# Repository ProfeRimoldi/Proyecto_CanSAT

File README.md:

# Proyecto CanSat – Base Aérea El Palomar

Sistema electrónico para misión tipo CanSat desarrollado en la EEST N°4 I Brigada Aérea El Palomar, orientado al diseño, validación y documentación de hardware y firmware para sistemas embarcados aeroespaciales.

Este repositorio centraliza el desarrollo de:

* Onboard Computer (OBC)
* Earth Station Dev Board
* Firmware ESP32
* Documentación técnica
* Revisiones de fabricación de PCB

---

## Estructura del proyecto

```text
Proyecto_CanSAT/
├── hardware/
│   ├── Onboard_Comp/
│   │   ├── kicad/
│   │   ├── outputs/
│   │   │   └── Rev_A/
│   │   └── docs/
│   │
│   └── Earth_Station/
│       ├── kicad/
│       ├── outputs/
│       └── docs/
│
├── firmware/
│
├── docs/
│
└── README.md
```

---

## Hardware

### Onboard Computer (OBC)

Computadora principal embarcada encargada de:

* adquisición de sensores
* telemetría
* control de misión
* gestión de eventos de vuelo
* integración con estación terrestre

Actualmente cuenta con:

* diseño PCB en KiCad
* esquemático jerárquico
* revisión formal de fabricación `Rev_A`
* Gerbers
* Drill files
* BOM
* PDF de esquemático
* renders e imágenes técnicas

---

### Earth Station Dev Board

Placa de desarrollo para estación terrestre destinada a:

* recepción de telemetría
* configuración de parámetros
* validación de comunicaciones
* integración de subsistemas

Actualmente cuenta con:

* diseño PCB en KiCad
* documentación estructurada
* revisión formal de fabricación `Rev_A`
* Gerbers
* Drill files
* BOM
* PDF de esquemático
* renders e imágenes técnicas

---

## Firmware

Desarrollo basado en ESP32 para:

* adquisición de datos
* control de sensores
* comunicaciones
* telemetría
* lógica de misión

Actualmente cuenta con:

* Firmware Test, verificador de enlace de comunicación LoRa entre los módulos.
* Muestra en pantalla, firmware dedicado a enviar los datos de aceleración en 3 ejes, y un código en Processing para visualizarlo.
* TestLED, para verificar el funcionamiento de los periféricos en la Earth Station Dev Board.

La estructura de firmware se encuentra en evolución y será versionada junto con las revisiones de hardware.

---

## Gestión de revisiones

Las revisiones de fabricación se organizan mediante:

```text
outputs/Rev_A/
outputs/Rev_B/
outputs/Rev_C/
```

permitiendo trazabilidad completa entre:

* diseño fuente
* fabricación real
* validaciones de laboratorio
* mejoras de revisión

---

## Objetivo

Mantener una metodología de desarrollo profesional para proyectos electrónicos aeroespaciales, con trazabilidad completa de hardware, firmware y documentación técnica.

---

## Autor

Damián Rimoldi
Ingeniería Electrónica – UTN FRH
GLT – Grupo de Lanzadores Tecnológicos
EEST N°4 I Brigada Aérea El Palomar

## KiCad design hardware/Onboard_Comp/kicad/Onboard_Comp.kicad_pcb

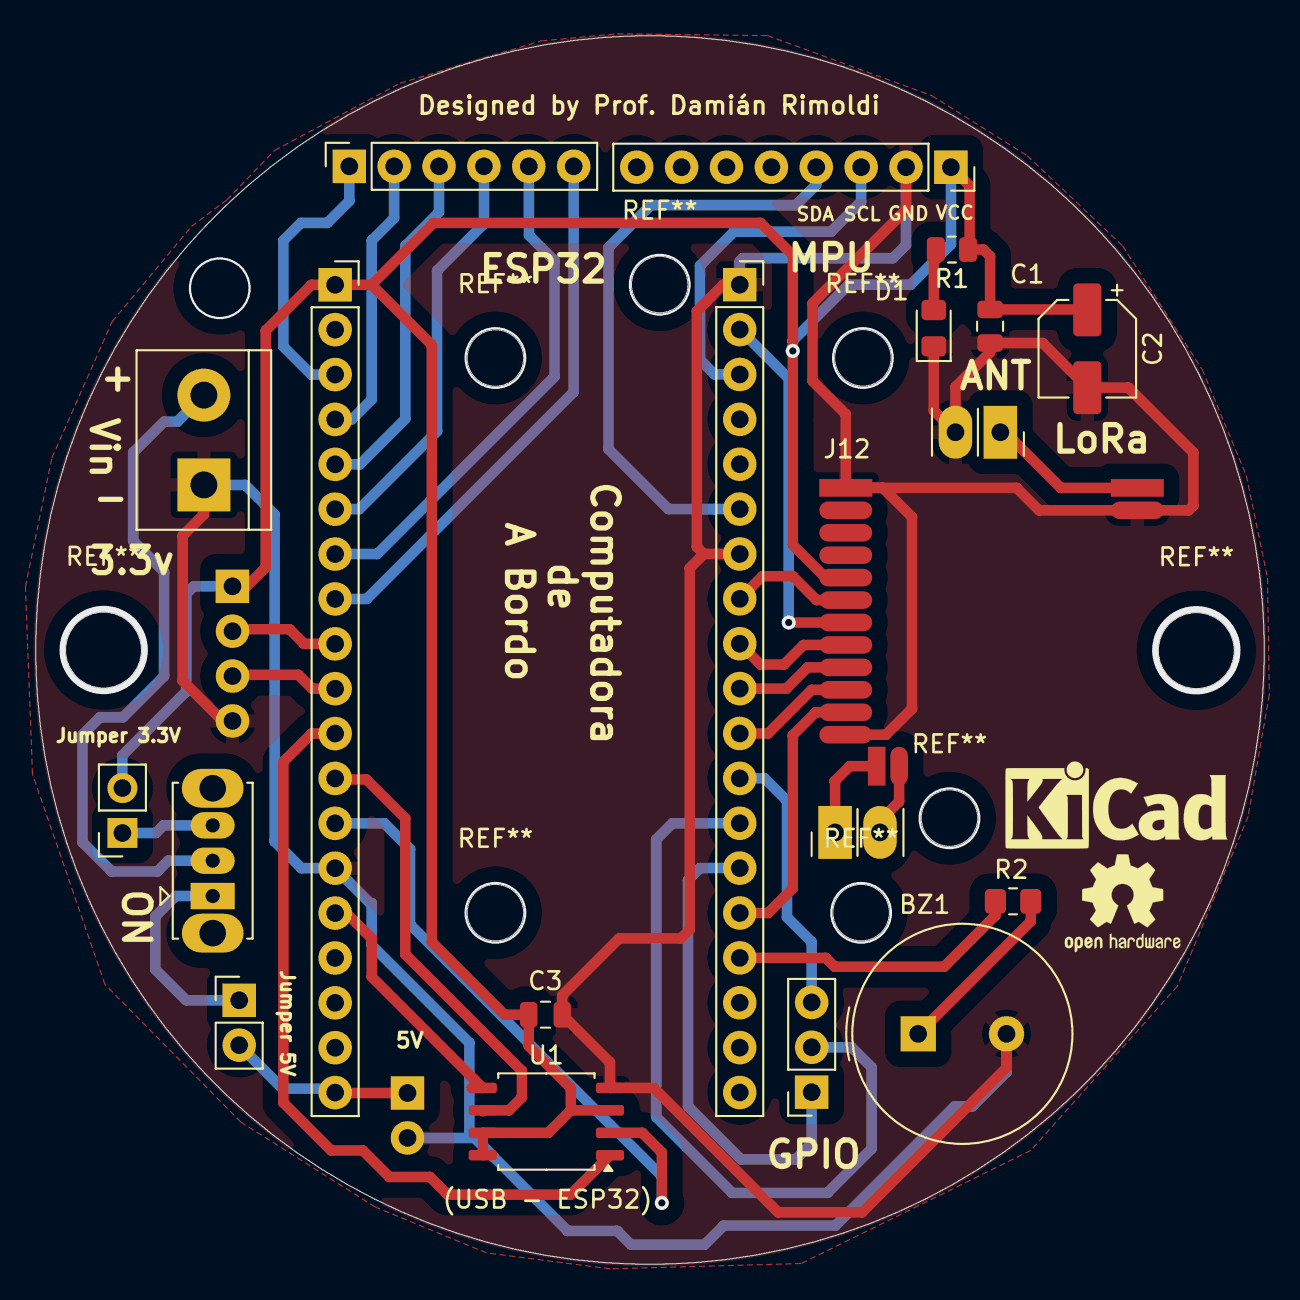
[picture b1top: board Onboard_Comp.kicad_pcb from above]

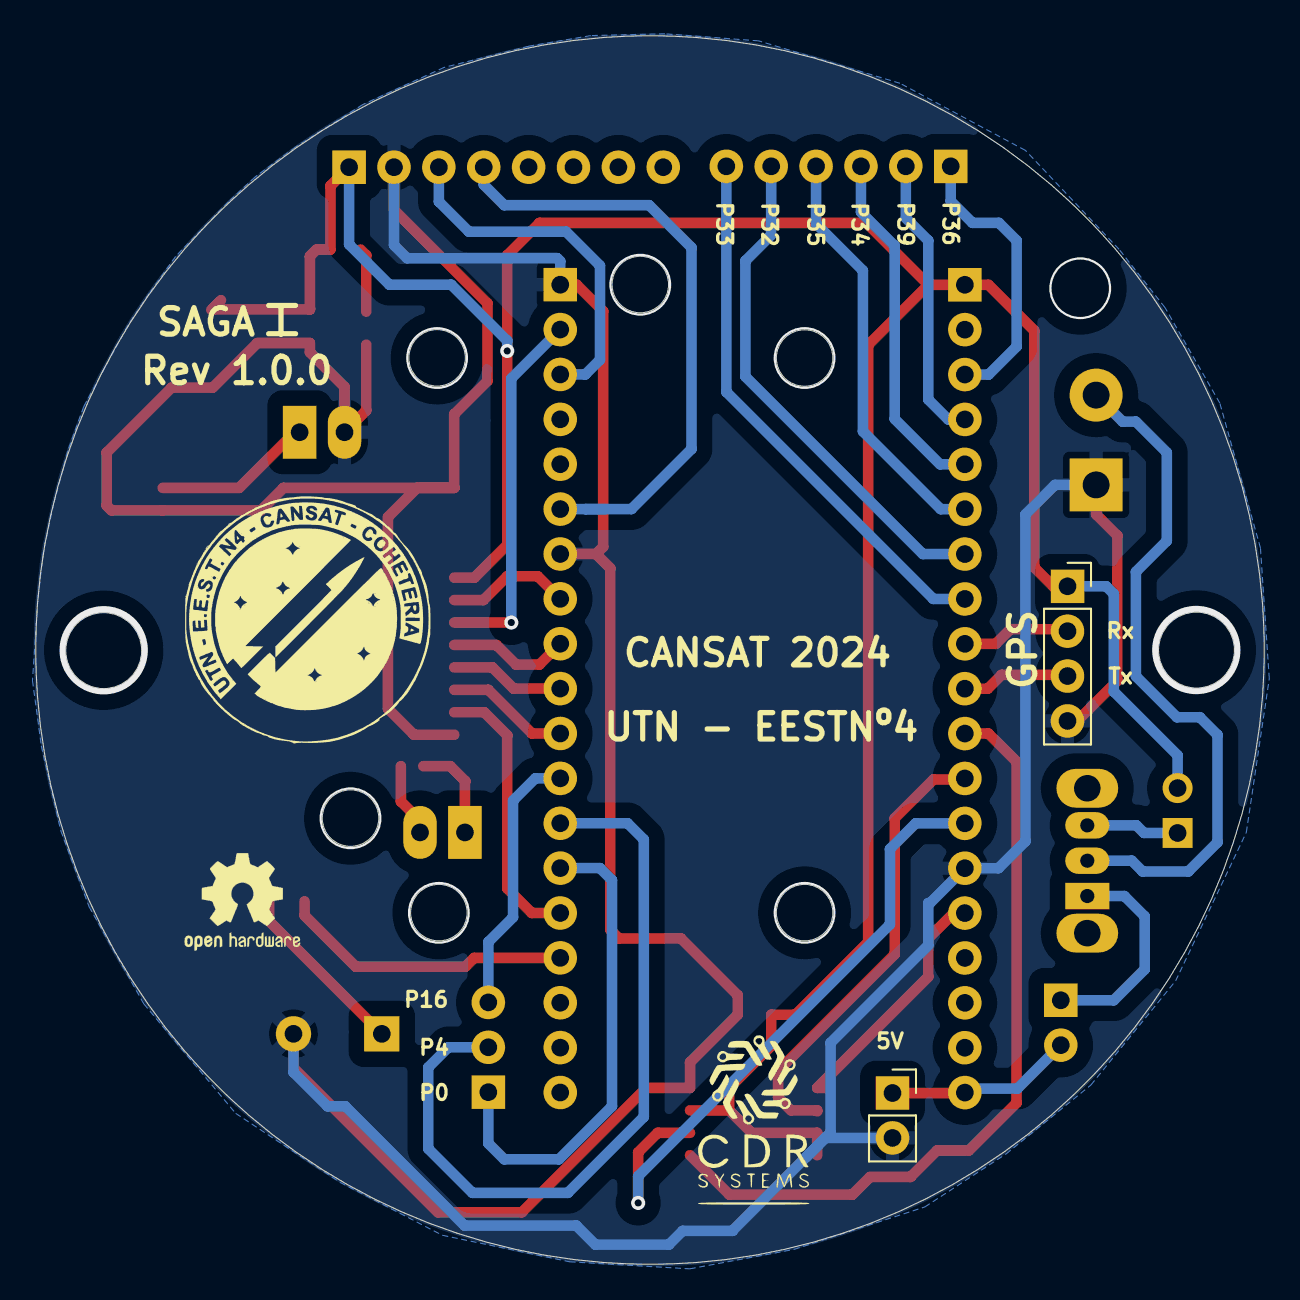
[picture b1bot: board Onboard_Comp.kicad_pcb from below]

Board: 2 copper layers, 69.5 x 69.5 mm, 24 parts (2 on the bottom side), 35 nets.

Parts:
BZ1: Buzzer; Buzzer_TDK_PS1240P02BT_D12.2mm_H6.5mm
C1: 100nF; C_0805_2012Metric
C2: 100uF; CP_Elec_5x3.9
C3: C_Polarized_Small; C_0805_2012Metric
D1: LED; LED_0805_2012Metric_Pad1.15x1.40mm_HandSolder
J1: SOCKET_UP; PinSocket_1x02_P2.54mm_Vertical
J4, J8: PLACA; PinHeader_1x02_P1.27mm_Vertical
J7: HEADER_DOWN; PinHeader_1x02_P2.54mm_Vertical
J12: PLACA; PinHeader_1x12_P1.27mm_Vertical
J13: Conn_01x08_SocketMPU; PinSocket_1x08_P2.54mm_Vertical
J14: Conn_01x04_Socket; PinSocket_1x04_P2.54mm_Vertical
J15: Screw_Terminal_01x02; TerminalBlock_bornier-2_P5.08mm
J16, J21: Conn_01x02; PinSocket_1x02_P2.54mm_Vertical
J17: Conn_01x06_Socket; PinSocket_1x06_P2.54mm_Vertical
J18: Conn_01x02; PinHeader_1x02_P2.54mm_Vertical
J19: Conn_01x03; PinSocket_1x03_P2.54mm_Vertical
R1: 1K; R_0805_2012Metric
R2: R; R_0805_2012Metric_Pad1.20x1.40mm_HandSolder
SW1: SW_SPDT; SW_Slide_SPDT_Straight_CK_OS102011MS2Q
U1: 25CSM04xxSN; SOIC-8_5.23x5.23mm_P1.27mm
esp1, esp32_1: Conn_01x19_Pin; PinSocket_1x19_P2.54mm_Vertical

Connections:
5v: J16.1, J18.2, esp1.19
ANTENA: J1.1, J4.1
BUZZ: R2.2, esp32_1.16
DIO0: J12.10, esp32_1.11
DIO4: J7.1, J8.1
DIO5: J7.2, J8.2
GND: BZ1.2 (-), C1.2, C2.2, C3.2, D1.1 (K), J1.2, J4.2, J12.1, J12.12, J13.2, J14.4, J15.1, J16.2, U1.4 (V_{SS}), esp1.14, esp32_1.1, esp32_1.7
GPIO0: J19.1, esp32_1.14
GPIO4: J19.2, esp32_1.13
GPIO16: J19.3, esp32_1.12
GPIO32: J17.5, esp1.7
GPIO33: J17.6, esp1.8
GPIO34: J17.3, esp1.5
GPIO35: J17.4, esp1.6
GPIO36: J17.1, esp1.3
GPIO39: J17.2, esp1.4
HCLK: U1.6 (SCK), esp1.12
HMISO: U1.2 (SO), esp1.13
HMOSI: U1.5 (SI), esp1.15
HSS: U1.1 (~CS), esp1.11
INVolt: J15.2, SW1.2 (B)
MISO: J12.6, esp32_1.8
MOSI: J12.7, esp32_1.2
NSS: J12.9, esp32_1.10
unnamed: BZ1.1 (+), R2.1
unnamed: D1.2 (A), R1.2
Pup: J18.1, SW1.1 (A)
REST: J12.11, esp32_1.15
RXGPS: J14.2, esp1.9
SCLMPU: J13.3, esp32_1.3
SDAMPU: J13.4, esp32_1.6
SLCK: J12.8, esp32_1.9
TXGPS: J14.3, esp1.10
VCC: C1.1, C2.1, C3.1, J12.5, J13.1, J14.1, J21.2, R1.1, U1.3 (~WP), U1.7 (~HOLD), U1.8 (V_{CC}), esp1.1
VCC1: J21.1, SW1.3 (C)

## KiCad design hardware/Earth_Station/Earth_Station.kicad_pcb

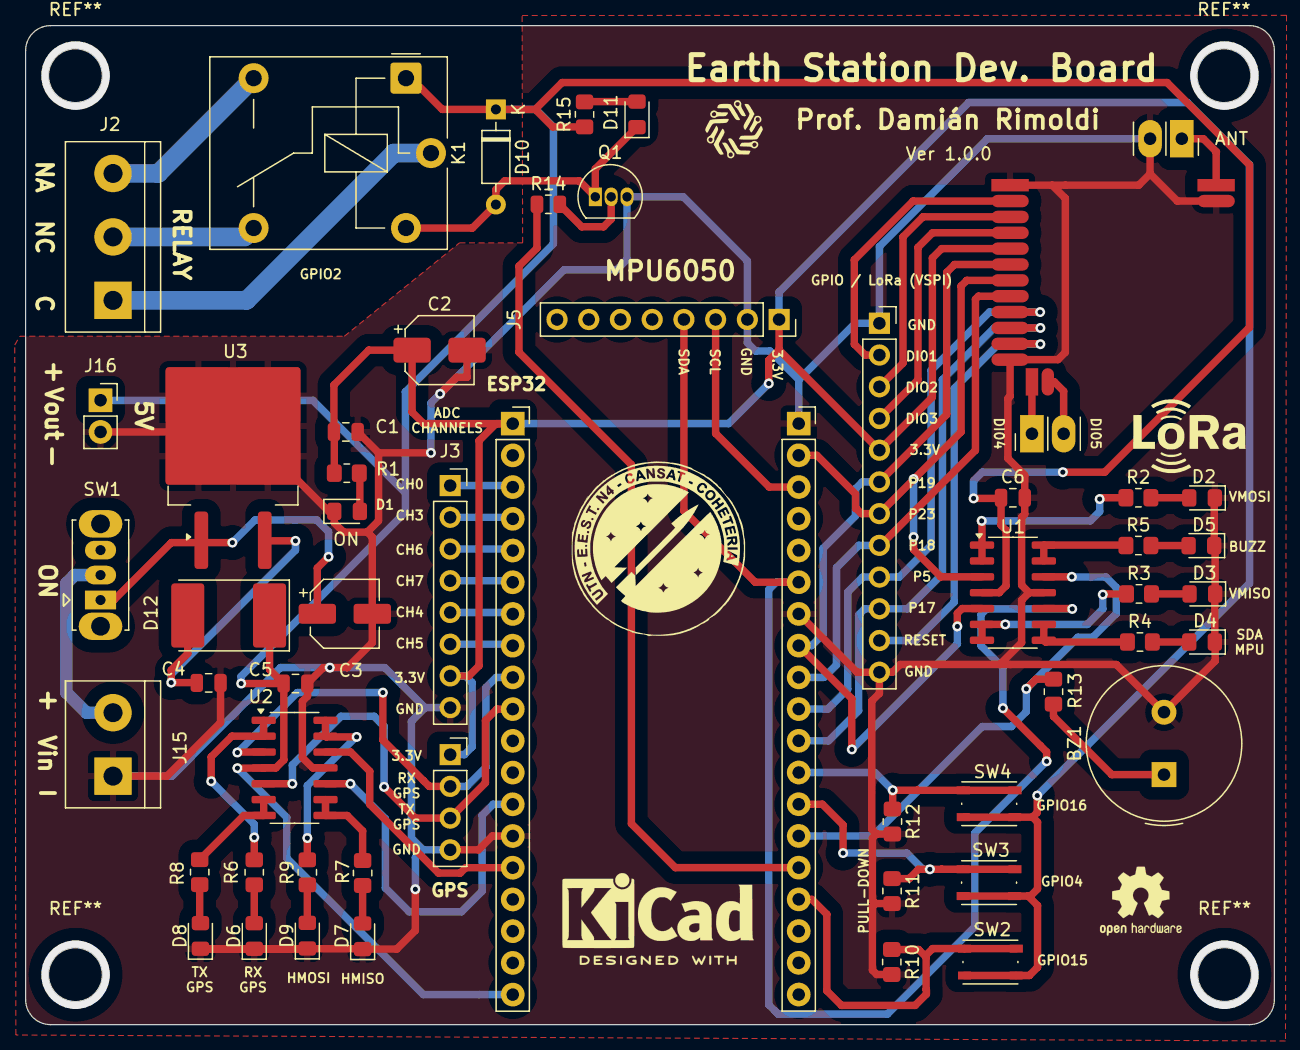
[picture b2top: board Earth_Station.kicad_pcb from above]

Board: 2 copper layers, 100.0 x 80.0 mm, 57 parts (0 on the bottom side), 59 nets.

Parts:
BZ1: Buzzer; Buzzer_TDK_PS1240P02BT_D12.2mm_H6.5mm
C1, C4, C5, C6: 100nF; C_0805_2012Metric
C2: 100uF; CP_Elec_5x3
C3: 10uF; CP_Elec_5x3.9
D1, D2, D3, D4, D5, D6, D7, D8, D9, D11: LED; LED_0805_2012Metric_Pad1.15x1.40mm_HandSolder
D10: 1N4148; D_DO-35_SOD27_P7.62mm_Horizontal
D12: SS34; D_3220_8050Metric_Pad2.65x5.15mm_HandSolder
J1: SOCKET_UP; PinSocket_1x02_P2.54mm_Vertical
J2: Screw_Terminal_01x03; TerminalBlock_bornier-3_P5.08mm
J3, J5: Conn_01x08; PinSocket_1x08_P2.54mm_Vertical
J4, J8: PLACA; PinHeader_1x02_P1.27mm_Vertical
J6: Conn_01x04; PinSocket_1x04_P2.54mm_Vertical
J7: HEADER_DOWN; PinHeader_1x02_P2.54mm_Vertical
J9: SOCKET_UP; PinSocket_1x12_P2.54mm_Vertical
J12: PLACA; PinHeader_1x12_P1.27mm_Vertical
J15: Screw_Terminal_01x02; TerminalBlock_bornier-2_P5.08mm
J16: Conn_01x02; PinSocket_1x02_P2.54mm_Vertical
K1: Relay_SPDT; Relay_SPDT_Finder_36.11
Q1: NPN; TO-92L_Inline
R1, R2, R3, R4, R5, R6, R7, R8, R9, R10, R11, R12, R15: 1K; R_0805_2012Metric_Pad1.20x1.40mm_HandSolder
R13: R; R_0805_2012Metric_Pad1.20x1.40mm_HandSolder
R14: R; R_0805_2012Metric
SW1: SW_SPDT; SW_Slide_SPDT_Straight_CK_OS102011MS2Q
SW2, SW3, SW4: SW_Push_Dual; SW_Push_1P1T_NO_Vertical_Wuerth_434133025816
U1, U2: LM324A; SOIC-14_3.9x8.7mm_P1.27mm
U3: L7805; TO-263-2
esp1, esp32_1: Conn_01x19_Pin; PinSocket_1x19_P2.54mm_Vertical

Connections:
5v: C5.1, C6.1, D10.1 (K), D12.1 (K), J16.1, K1.A1, R15.1, U1.4 (V+), U2.4 (V+), esp1.19
ANTENA: J1.1, J4.1
BUZZ: R13.2, U1.12 (+), esp32_1.14
CLOAD: J2.1, K1.11
DIO0: J9.10, J12.10, esp32_1.11
DIO1: J9.2, J12.2
DIO2: J9.3, J12.3
DIO3: J9.4, J12.4
DIO4: J7.1, J8.1
DIO5: J7.2, J8.2
GND: BZ1.2 (-), C1.2, C2.2, C3.2, C4.2, C5.2, C6.2, D1.1 (K), D2.1 (K), D3.1 (K), D4.1 (K), D5.1 (K), D6.1 (K), D7.1 (K), D8.1 (K), D9.1 (K), J1.2, J3.8, J4.2, J5.2, J6.4, J9.1, J9.12, J12.1, J12.12, J15.1, J16.2, Q1.3 (E), R10.2, R11.2, R12.2, U1.11 (V-), U2.11 (V-), U3.2 (GND), esp1.14, esp32_1.1, esp32_1.7
GPIO2: R14.1, esp32_1.15
GPIO4: R11.1, SW3.1, esp32_1.13
GPIO15: R10.1, SW2.1, esp32_1.16
GPIO16: R12.1, SW4.1, esp32_1.12
GPIO32: J3.5, esp1.7
GPIO33: J3.6, esp1.8
GPIO34: J3.3, esp1.5
GPIO35: J3.4, esp1.6
GPIO36: J3.1, esp1.3
GPIO39: J3.2, esp1.4
HMISO: U2.10 (+), esp1.13
HMOSI: U2.12 (+), esp1.15
INVolt: J15.2, SW1.2 (B)
MISO: J9.6, J12.6, U1.5 (+), esp32_1.8
MOSI: J9.7, J12.7, U1.3 (+), esp32_1.2
NALOAD: J2.3, K1.14
NCLOAD: J2.2, K1.12
NSS: J9.9, J12.9, esp32_1.10
unnamed: BZ1.1 (+), R13.1
unnamed: D1.2 (A), R1.2
unnamed: D2.2 (A), R2.2
unnamed: D3.2 (A), R3.2
unnamed: D4.2 (A), R4.2
unnamed: D5.2 (A), R5.2
unnamed: D6.2 (A), R6.2
unnamed: D7.2 (A), R7.2
unnamed: D8.2 (A), R8.2
unnamed: D9.2 (A), R9.2
unnamed: D10.2 (A), D11.1 (K), K1.A2, Q1.1 (C)
unnamed: D11.2 (A), R15.2
unnamed: C4.1, D12.2 (A), U3.3 (OUT)
unnamed: Q1.2 (B), R14.2
unnamed: R2.1, U1.1, U1.2 (-)
unnamed: R3.1, U1.6 (-), U1.7
unnamed: R4.1, U1.8, U1.9 (-)
unnamed: R5.1, U1.13 (-), U1.14
unnamed: R6.1, U2.1, U2.2 (-)
unnamed: R8.1, U2.6 (-), U2.7
unnamed: R7.1, U2.8, U2.9 (-)
unnamed: R9.1, U2.13 (-), U2.14
REST: J9.11, J12.11
RXGPS: J6.2, U2.3 (+), esp1.9
SCLMPU: J5.3, esp32_1.3
SDAMPU: J5.4, U1.10 (+), esp32_1.6
SLCK: J9.8, J12.8, esp32_1.9
TXGPS: J6.3, U2.5 (+), esp1.10
VCC: C1.1, C2.1, J3.7, J5.1, J6.1, J9.5, J12.5, R1.1, SW2.2, SW3.2, SW4.2, esp1.1
VregIn: C3.1, SW1.1 (A), U3.1 (IN)

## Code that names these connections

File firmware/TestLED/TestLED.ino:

//      Código de Testeo para la placa Earth Station Dev. Board.
//                  
//Prof. Damián Rimoldi              Oct. 21, 2024

#define RxGPS 25
#define TxGPS 26

#define HMOSI 13
#define HMISO 12

#define BUZZ 0

#define VMISO 19
#define VMOSI 23

#define SDAMPU 21

#define RELAY 2

int tiempo1 =500;
int tiempo2 =200;
int tiempo3 =100;
int tiempo4 =50;
int tiempo5 =20;
int veces =5;
void setup() {
  pinMode(RxGPS, OUTPUT);
  pinMode(TxGPS, OUTPUT);
  pinMode(HMOSI, OUTPUT);
  pinMode(HMISO, OUTPUT);
  pinMode(BUZZ, OUTPUT);
  pinMode(VMISO, OUTPUT);
  pinMode(VMOSI, OUTPUT);
  pinMode(SDAMPU, OUTPUT);
  pinMode(RELAY, OUTPUT);
  

  Serial.begin(9600);
}

void loop() {
 /* Serial.println("Indique el tiempo de secuencia: ");
  while(Serial.available()) {};
  tiempo = Serial.parseInt();
  Serial.println("Indique las repeticiones de secuencia: ");
  while(Serial.available()) {};
  veces = Serial.parseInt();*/
  for(int i=0; i<veces; i++)
    {
      digitalWrite(VMOSI, HIGH);
      delay (tiempo1);
      digitalWrite(VMOSI, LOW);
      digitalWrite(BUZZ, HIGH);
      delay (tiempo1);
      digitalWrite(BUZZ, LOW);
      digitalWrite(VMISO, HIGH);
      delay (tiempo1);
      digitalWrite(VMISO, LOW);
      digitalWrite(SDAMPU, HIGH);
      delay (tiempo1);
      digitalWrite(SDAMPU, LOW);
      digitalWrite(TxGPS, HIGH);
      delay (tiempo1);
      digitalWrite(TxGPS, LOW);
      digitalWrite(RxGPS, HIGH);
      delay (tiempo1);
      digitalWrite(RxGPS, LOW);
      digitalWrite(HMOSI, HIGH);
      delay (tiempo1);
      digitalWrite(HMOSI, LOW);
      digitalWrite(HMISO, HIGH);
      delay (tiempo1);
      digitalWrite(HMISO, LOW);
      digitalWrite(RELAY, HIGH);
      delay (tiempo1);
      digitalWrite(RELAY, LOW);
      }
  for(int i=0; i<veces; i++)
    {
      digitalWrite(VMOSI, HIGH);
      delay (tiempo2);
      digitalWrite(VMOSI, LOW);
      digitalWrite(BUZZ, HIGH);
      delay (tiempo2);
      digitalWrite(BUZZ, LOW);
      digitalWrite(VMISO, HIGH);
      delay (tiempo2);
      digitalWrite(VMISO, LOW);
      digitalWrite(SDAMPU, HIGH);
      delay (tiempo2);
      digitalWrite(SDAMPU, LOW);
      digitalWrite(TxGPS, HIGH);
      delay (tiempo2);
      digitalWrite(TxGPS, LOW);
      digitalWrite(RxGPS, HIGH);
      delay (tiempo2);
      digitalWrite(RxGPS, LOW);
      digitalWrite(HMOSI, HIGH);
      delay (tiempo2);
      digitalWrite(HMOSI, LOW);
      digitalWrite(HMISO, HIGH);
      delay (tiempo2);
      digitalWrite(HMISO, LOW);
      digitalWrite(RELAY, HIGH);
      delay (tiempo2);
      digitalWrite(RELAY, LOW);
      }
  for(int i=0; i<veces; i++)
    {
      digitalWrite(VMOSI, HIGH);
      delay (tiempo3);
      digitalWrite(VMOSI, LOW);
      digitalWrite(BUZZ, HIGH);
      delay (tiempo3);
      digitalWrite(BUZZ, LOW);
      digitalWrite(VMISO, HIGH);
      delay (tiempo3);
      digitalWrite(VMISO, LOW);
      digitalWrite(SDAMPU, HIGH);
      delay (tiempo3);
      digitalWrite(SDAMPU, LOW);
      digitalWrite(TxGPS, HIGH);
      delay (tiempo3);
      digitalWrite(TxGPS, LOW);
      digitalWrite(RxGPS, HIGH);
      delay (tiempo3);
      digitalWrite(RxGPS, LOW);
      digitalWrite(HMOSI, HIGH);
      delay (tiempo3);
      digitalWrite(HMOSI, LOW);
      digitalWrite(HMISO, HIGH);
      delay (tiempo3);
      digitalWrite(HMISO, LOW);
      digitalWrite(RELAY, HIGH);
      delay (tiempo3);
      digitalWrite(RELAY, LOW);
      }
  for(int i=0; i<veces; i++)
    {
      digitalWrite(VMOSI, HIGH);
      delay (tiempo4);
      digitalWrite(VMOSI, LOW);
      digitalWrite(BUZZ, HIGH);
      delay (tiempo4);
      digitalWrite(BUZZ, LOW);
      digitalWrite(VMISO, HIGH);
      delay (tiempo4);
      digitalWrite(VMISO, LOW);
      digitalWrite(SDAMPU, HIGH);
      delay (tiempo4);
      digitalWrite(SDAMPU, LOW);
      digitalWrite(TxGPS, HIGH);
      delay (tiempo4);
      digitalWrite(TxGPS, LOW);
      digitalWrite(RxGPS, HIGH);
      delay (tiempo4);
      digitalWrite(RxGPS, LOW);
      digitalWrite(HMOSI, HIGH);
      delay (tiempo4);
      digitalWrite(HMOSI, LOW);
      digitalWrite(HMISO, HIGH);
      delay (tiempo4);
      digitalWrite(HMISO, LOW);
      digitalWrite(RELAY, HIGH);
      delay (tiempo4);
      digitalWrite(RELAY, LOW);
      }
  for(int i=0; i<10; i++)
    {
      digitalWrite(VMOSI, HIGH);
      delay (tiempo5);
      digitalWrite(VMOSI, LOW);
      digitalWrite(BUZZ, HIGH);
      delay (tiempo5);
      digitalWrite(BUZZ, LOW);
      digitalWrite(VMISO, HIGH);
      delay (tiempo5);
      digitalWrite(VMISO, LOW);
      digitalWrite(SDAMPU, HIGH);
      delay (tiempo5);
      digitalWrite(SDAMPU, LOW);
      digitalWrite(TxGPS, HIGH);
      delay (tiempo5);
      digitalWrite(TxGPS, LOW);
      digitalWrite(RxGPS, HIGH);
      delay (tiempo5);
      digitalWrite(RxGPS, LOW);
      digitalWrite(HMOSI, HIGH);
      delay (tiempo5);
      digitalWrite(HMOSI, LOW);
      digitalWrite(HMISO, HIGH);
      delay (tiempo5);
      digitalWrite(HMISO, LOW);
      digitalWrite(RELAY, HIGH);
      delay (tiempo5);
      digitalWrite(RELAY, LOW);
      }
  //LEDTEST (tiempo, veces);
  // put your main code here, to run repeatedly:

}
/*LEDTEST (int t, int v)
  {
    for(int i=0; i<v; i++)
    {
      digitalWrite(VMOSI, HIGH);
      delay (t);
      digitalWrite(VMOSI, LOW);
      digitalWrite(BUZZ, HIGH);
      delay (t);
      digitalWrite(BUZZ, LOW);
      digitalWrite(VMISO, HIGH);
      delay (t);
      digitalWrite(VMISO, LOW);
      digitalWrite(SDAMPU, HIGH);
      delay (t);
      digitalWrite(SDAMPU, LOW);
      digitalWrite(TxGPS, HIGH);
      delay (t);
      digitalWrite(TxGPS, LOW);
      digitalWrite(RxGPS, HIGH);
      delay (t);
      digitalWrite(RxGPS, LOW);
      digitalWrite(HMOSI, HIGH);
      delay (t);
      digitalWrite(HMOSI, LOW);
      digitalWrite(HMISO, HIGH);
      delay (t);
      digitalWrite(HMISO, LOW);
      digitalWrite(RELAY, HIGH);
      delay (t);
      digitalWrite(RELAY, LOW);
      }

}*/

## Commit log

2026-04-16 Estructura inicial del proyecto CanSat
2026-04-16 Cambio README.md y Prueba SSH
2026-04-16 Add initial hardware design: Onboard Computer and Earth Station KiCad projects
2026-04-17 Reorganize Onboard Computer KiCad project structure
2026-04-17 Reorganize Earth Station KiCad project structure
2026-04-17 Add documentation structure for hardware outputs and technical docs
2026-04-17 Fix root gitignore configuration
2026-04-19 Add Onboard Computer Rev A fabrication outputs
2026-04-19 Update main README with project structure hardware documentation
2026-04-19 Add settings structure for hardware outputs and technical docs
2026-04-29 Agrego firmware de prueba
2026-04-29 Actualizo README.md general con la descripcion del firmware agregado
2026-04-29 Agrego archivo README.md especifico del firmware
2026-04-29 Agrego README. general en documentacion
2026-04-29 Agrego documentacion de la arquitectura del sistema
2026-06-26 Actualizo archivo README.md
2026-06-26 Actualizo README.md
